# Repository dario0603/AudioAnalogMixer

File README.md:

# Analog Audio Mixer

## Overview

Design and development of a **modular analog audio mixer**, combining circuit simulation and PCB design. The project focuses on audio signal conditioning, equalization, level control, and the integration of multiple input channels into a modular mixer architecture.

The design is divided into two main development areas:

- **LTspice simulations:** individual analog circuit blocks are simulated and evaluated before hardware implementation.
- **KiCad designs:** modular PCB boards are developed to organize the mixer circuitry into functional sections.

The current design includes microphone/line signal conditioning, a three-band equalizer, level and FX-send circuitry, a clipping indicator, and a four-channel mixer board.

The project is still under development. Circuit design, simulation, and PCB integration are ongoing, and the current files should be considered work in progress rather than a finalized hardware design.

## System Architecture

The mixer is organized into modular functional blocks. This approach makes it possible to develop and test each section independently before integrating the complete system.
The input stage provides microphone and line-level signal conditioning. Separate configurations are included for a single microphone/line channel and for two line-level channels, intended for left and right stereo signals.

The signal-conditioning section includes:

- Microphone/line preamplification.
- Three-band tone control.
- Output-level adjustment.
- FX-send circuitry.

### 1. Microphone/Line Preamplifier Circuit

The microphone/line preamplifier circuit provides input signal conditioning and amplification for low-level microphone signals and line-level audio sources. It is designed to adapt different input signal levels to the following stages of the mixer, ensuring proper signal amplification and compatibility with the audio processing circuitry.

### 2. Three-Band Equalizer

The three-band equalizer provides independent control over the low-, mid-, and high-frequency portions of the audio spectrum.

The frequency response is evaluated through LTspice AC analysis. Different equalizer settings are compared to investigate how the circuit affects the audio signal across the frequency range.

### 3. Mixer Unit

This stage combines the signals processed by the input stages (microphone/line preamplifier and three-band equalizer), summing the individual channels to generate the final audio output. The output is provided in differential mode through two dedicated buffer amplifiers, ensuring proper signal driving capability and output impedance.

### 4. Clipping Indicator

A dedicated clipping-indicator circuit is included in the LTspice project.

The circuit uses an LM393 comparator model to detect signal levels approaching the selected clipping threshold. The output can be used to drive an LED, providing a visual indication of excessive signal amplitude.

The comparator circuit is simulated separately to allow its operation and threshold behavior to be evaluated independently of the complete mixer.

## Simulations

### 1. Three-Band Equalizer

**Frequency Response Analysis**

The frequency response of the three-band equalizer is analyzed for different control settings, including low-frequency, mid-frequency, and high-frequency attenuation.

| Low-frequency cut | Mid-frequency cut | High-frequency cut |
|:---:|:---:|:---:|
|  |  |  |

**Flat Frequency Response Analysis**

The overall frequency response is evaluated with all equalizer controls set to their neutral positions.

**Monte Carlo Frequency Response Analysis**

A Monte Carlo analysis is performed to evaluate the effect of component tolerances on the equalizer response, considering 1% resistor tolerances (0603 package) and 10% ceramic X7R capacitor tolerances.

### 2. Microphone/Line Preamplifier

**AC Frequency Response Analysis**

The frequency response of the line and XLR preamplifier configurations is evaluated through LTspice AC analysis to characterize their behavior across the audio frequency range.

**Line Preamplifier:**

**XLR Preamplifier:**

**Transient Response Analysis – 5 kHz Differential Input**

A 5 kHz differential sinusoidal signal is applied to the XLR preamplifier to evaluate its transient response under maximum and minimum gain configurations.

**Input Signal:**

**Maximum Gain Configuration:**

**Minimum Gain Configuration:**

**Monte Carlo Transient Analysis**

A Monte Carlo simulation consisting of 300 runs is performed to evaluate the variability of the XLR preamplifier transient response due to component tolerances, considering both maximum and minimum gain configurations.

**Maximum Gain Configuration:**

**Minimum Gain Configuration:**

**Noise Analysis**

LTspice noise analysis is performed to evaluate the output noise spectral density of the preamplifier stages. Different operational-amplifier configurations are compared to investigate their noise contributions.

The noise simulations are still being refined, particularly regarding the accuracy of the operational-amplifier noise models and their consistency with datasheet specifications.

### 3. Mixer

**Transient Response Analysis**

Transient simulations are performed to evaluate the time-domain behavior of the mixer circuit.

**Monte Carlo Transient Analysis**

A Monte Carlo simulation consisting of 300 runs is performed to investigate output voltage variations caused by component tolerances.

.png)

## PCB Design

The PCB development is carried out in KiCad. The modular approach separates the main mixer board from the input signal-conditioning circuitry.

### 1. Four-Channel Mixer Board

The `4ChannelMixerBoard` project contains the PCB design and schematic for the four-channel mixer board.

The board is intended to provide the central platform for combining the individual audio channels.

### 2. Single-Channel Microphone/Line Board

The `SignalConditioning - OneChannel - Mic-Line` project contains the signal-conditioning design for a single microphone/line input channel.
The PCB layout brings the microphone/line preamplifier, three-band equalizer, level and FX-send circuitry, and power supply together on a single board.

The project includes the following schematic sections:

- Microphone/line preamplifier.
- Three-band equalizer.
- Level control and FX-send circuitry.
- Power supply.

### 3. Two-Channel Line Board

The `SignalConditioning - TwoChannels - R-L-Line` project contains a two-channel signal-conditioning configuration intended for right and left line-level signals.

Its schematic is organized around the same functional blocks as the single-channel version, adapted for a stereo input configuration.

## Repository Structure

```text
.
├── README.md
│
├── AudioMixer - LTSpice/
│   ├── 3bEq/
│   │   ├── AudioMixer - 3bEq.asc
│   │   ├── NE5532.sub
│   │   └── Montecarlo/
│   │
│   ├── ClippingLed/
│   │   ├── ClippingLed.asc
│   │   └── lm393.lib
│   │
│   └── Mic-Line amplifier/
│       ├── AudioMixer - Mic-Line-amp.asc
│       └── NE5532.sub
│
├── AudioMixer - ModularBoards/
│   ├── spec.txt
│   │
│   ├── 4ChannelMixerBoard/
│   │   ├── Mixer_circuit.kicad_pro
│   │   ├── Mixer_circuit.kicad_sch
│   │   └── Mixer_circuit.kicad_pcb
│   │
│   ├── SignalConditioning - OneChannel - Mic-Line/
│   │   ├── AudioMixer.kicad_pro
│   │   ├── AudioMixer.kicad_sch
│   │   ├── AudioMixer.kicad_pcb
│   │   ├── Mic-Line_preamp.kicad_sch
│   │   ├── 3_band_equalizer.kicad_sch
│   │   ├── Level_and_FXSend.kicad_sch
│   │   └── Power_supply.kicad_sch
│   │
│   └── SignalConditioning - TwoChannels - R-L-Line/
│       ├── AudioMixer.kicad_pro
│       ├── AudioMixer.kicad_sch
│       ├── AudioMixer.kicad_pcb
│       ├── Mic-Line_preamp.kicad_sch
│       ├── 3_band_equalizer.kicad_sch
│       ├── Level_and_FXSend.kicad_sch
│       └── Power_supply.kicad_sch
│
└── img/
```

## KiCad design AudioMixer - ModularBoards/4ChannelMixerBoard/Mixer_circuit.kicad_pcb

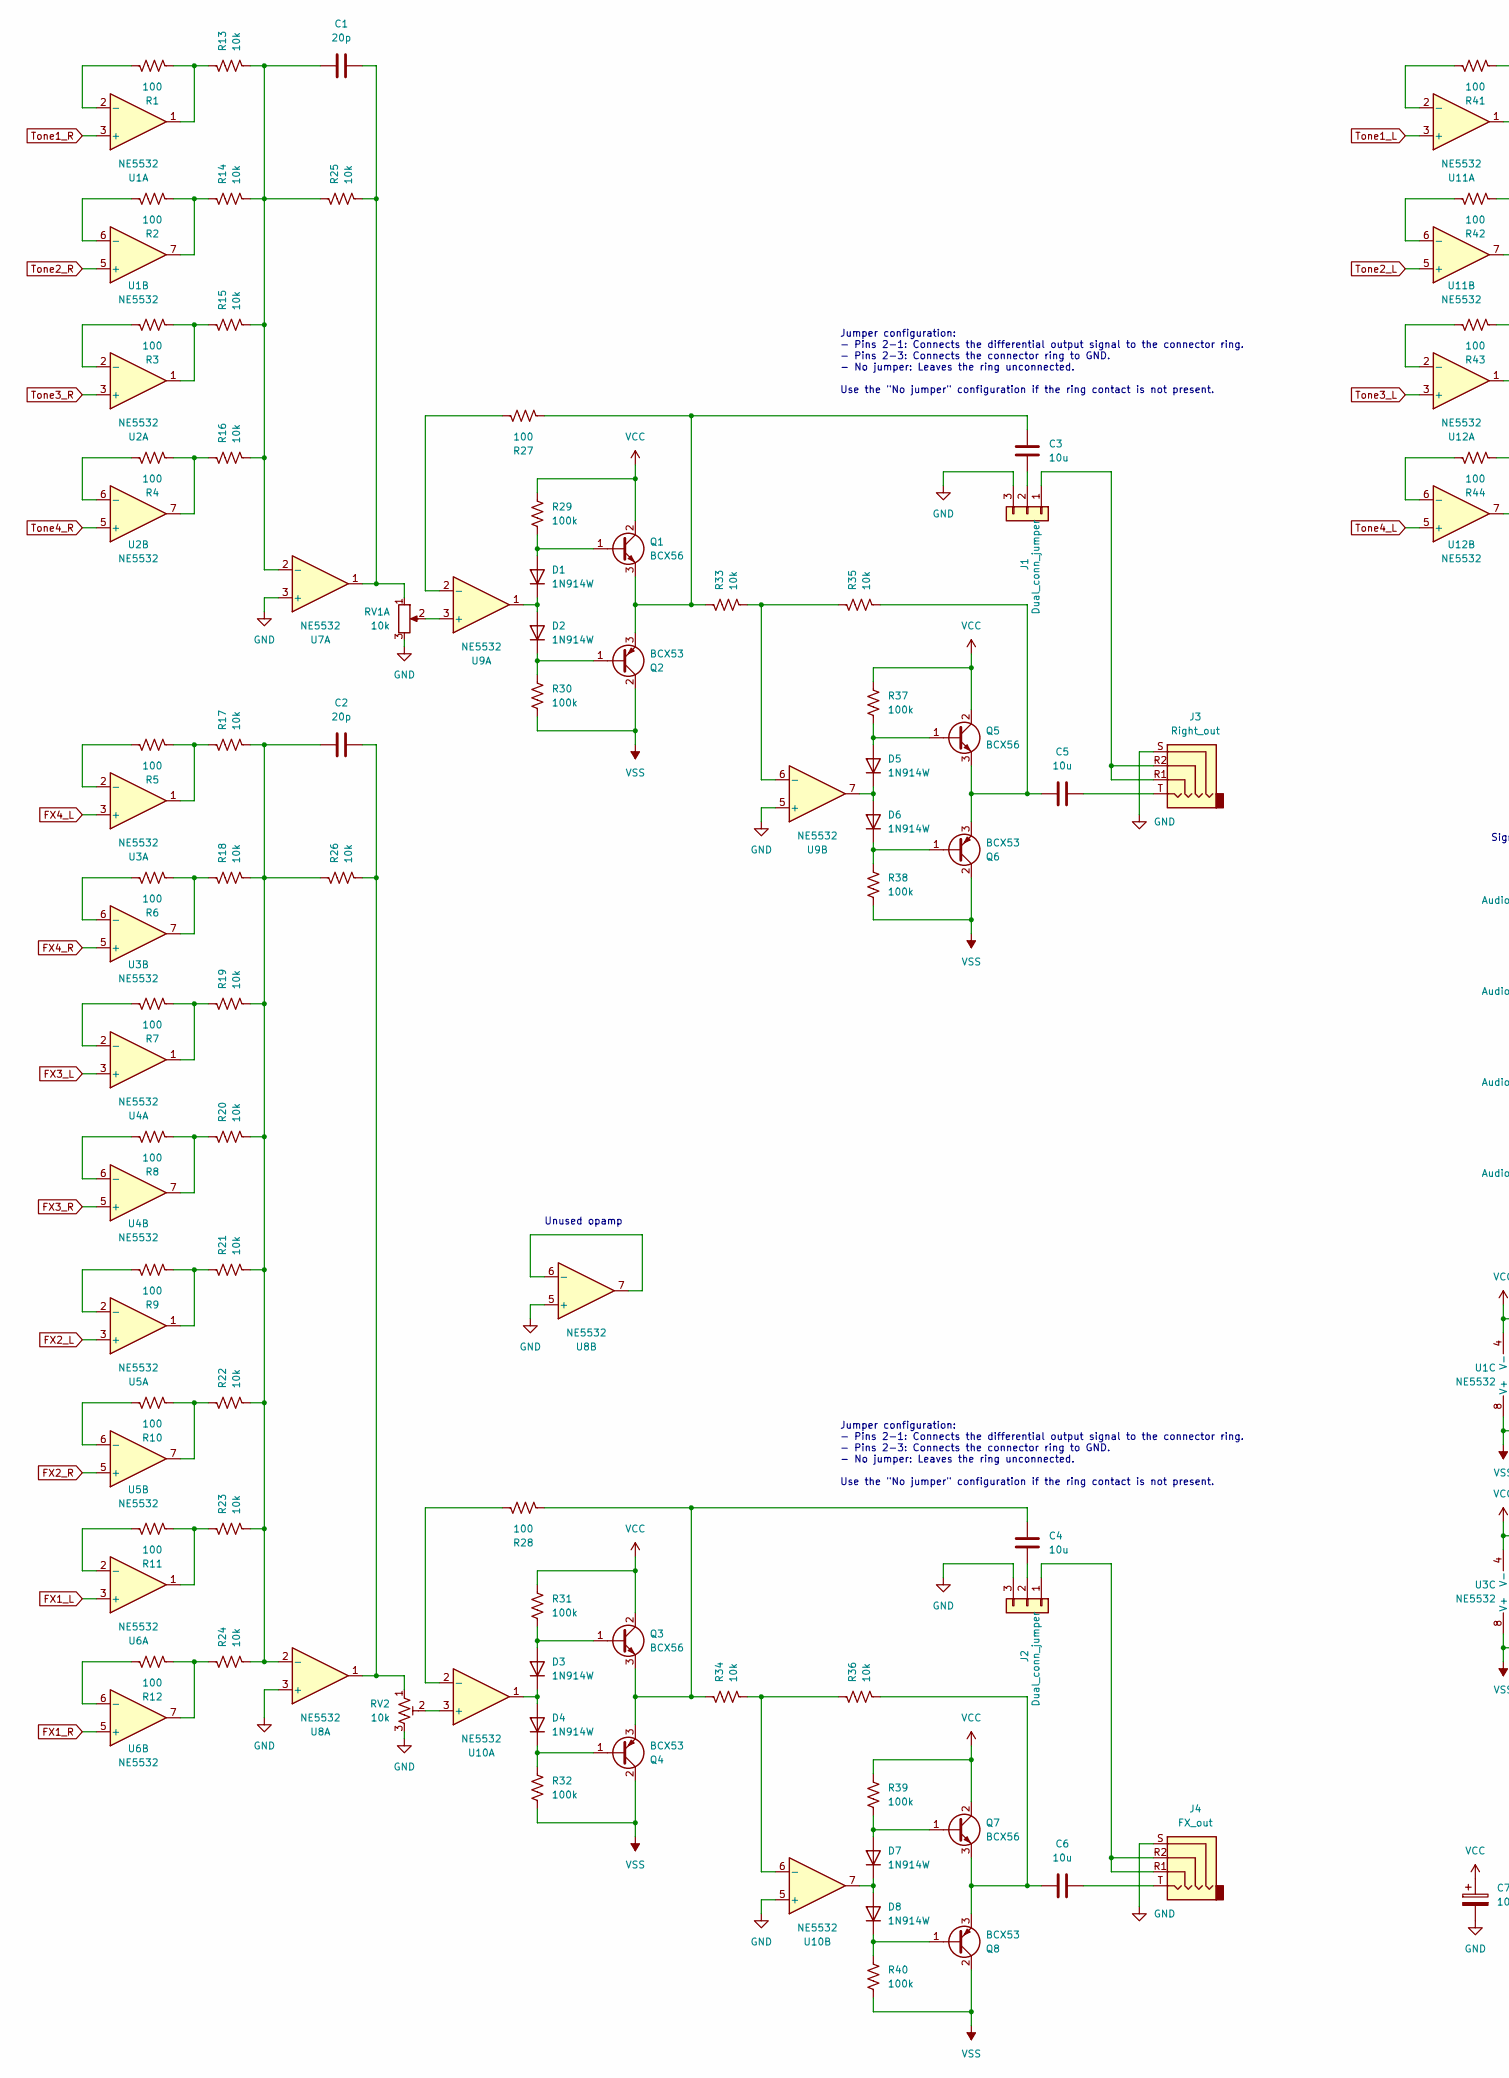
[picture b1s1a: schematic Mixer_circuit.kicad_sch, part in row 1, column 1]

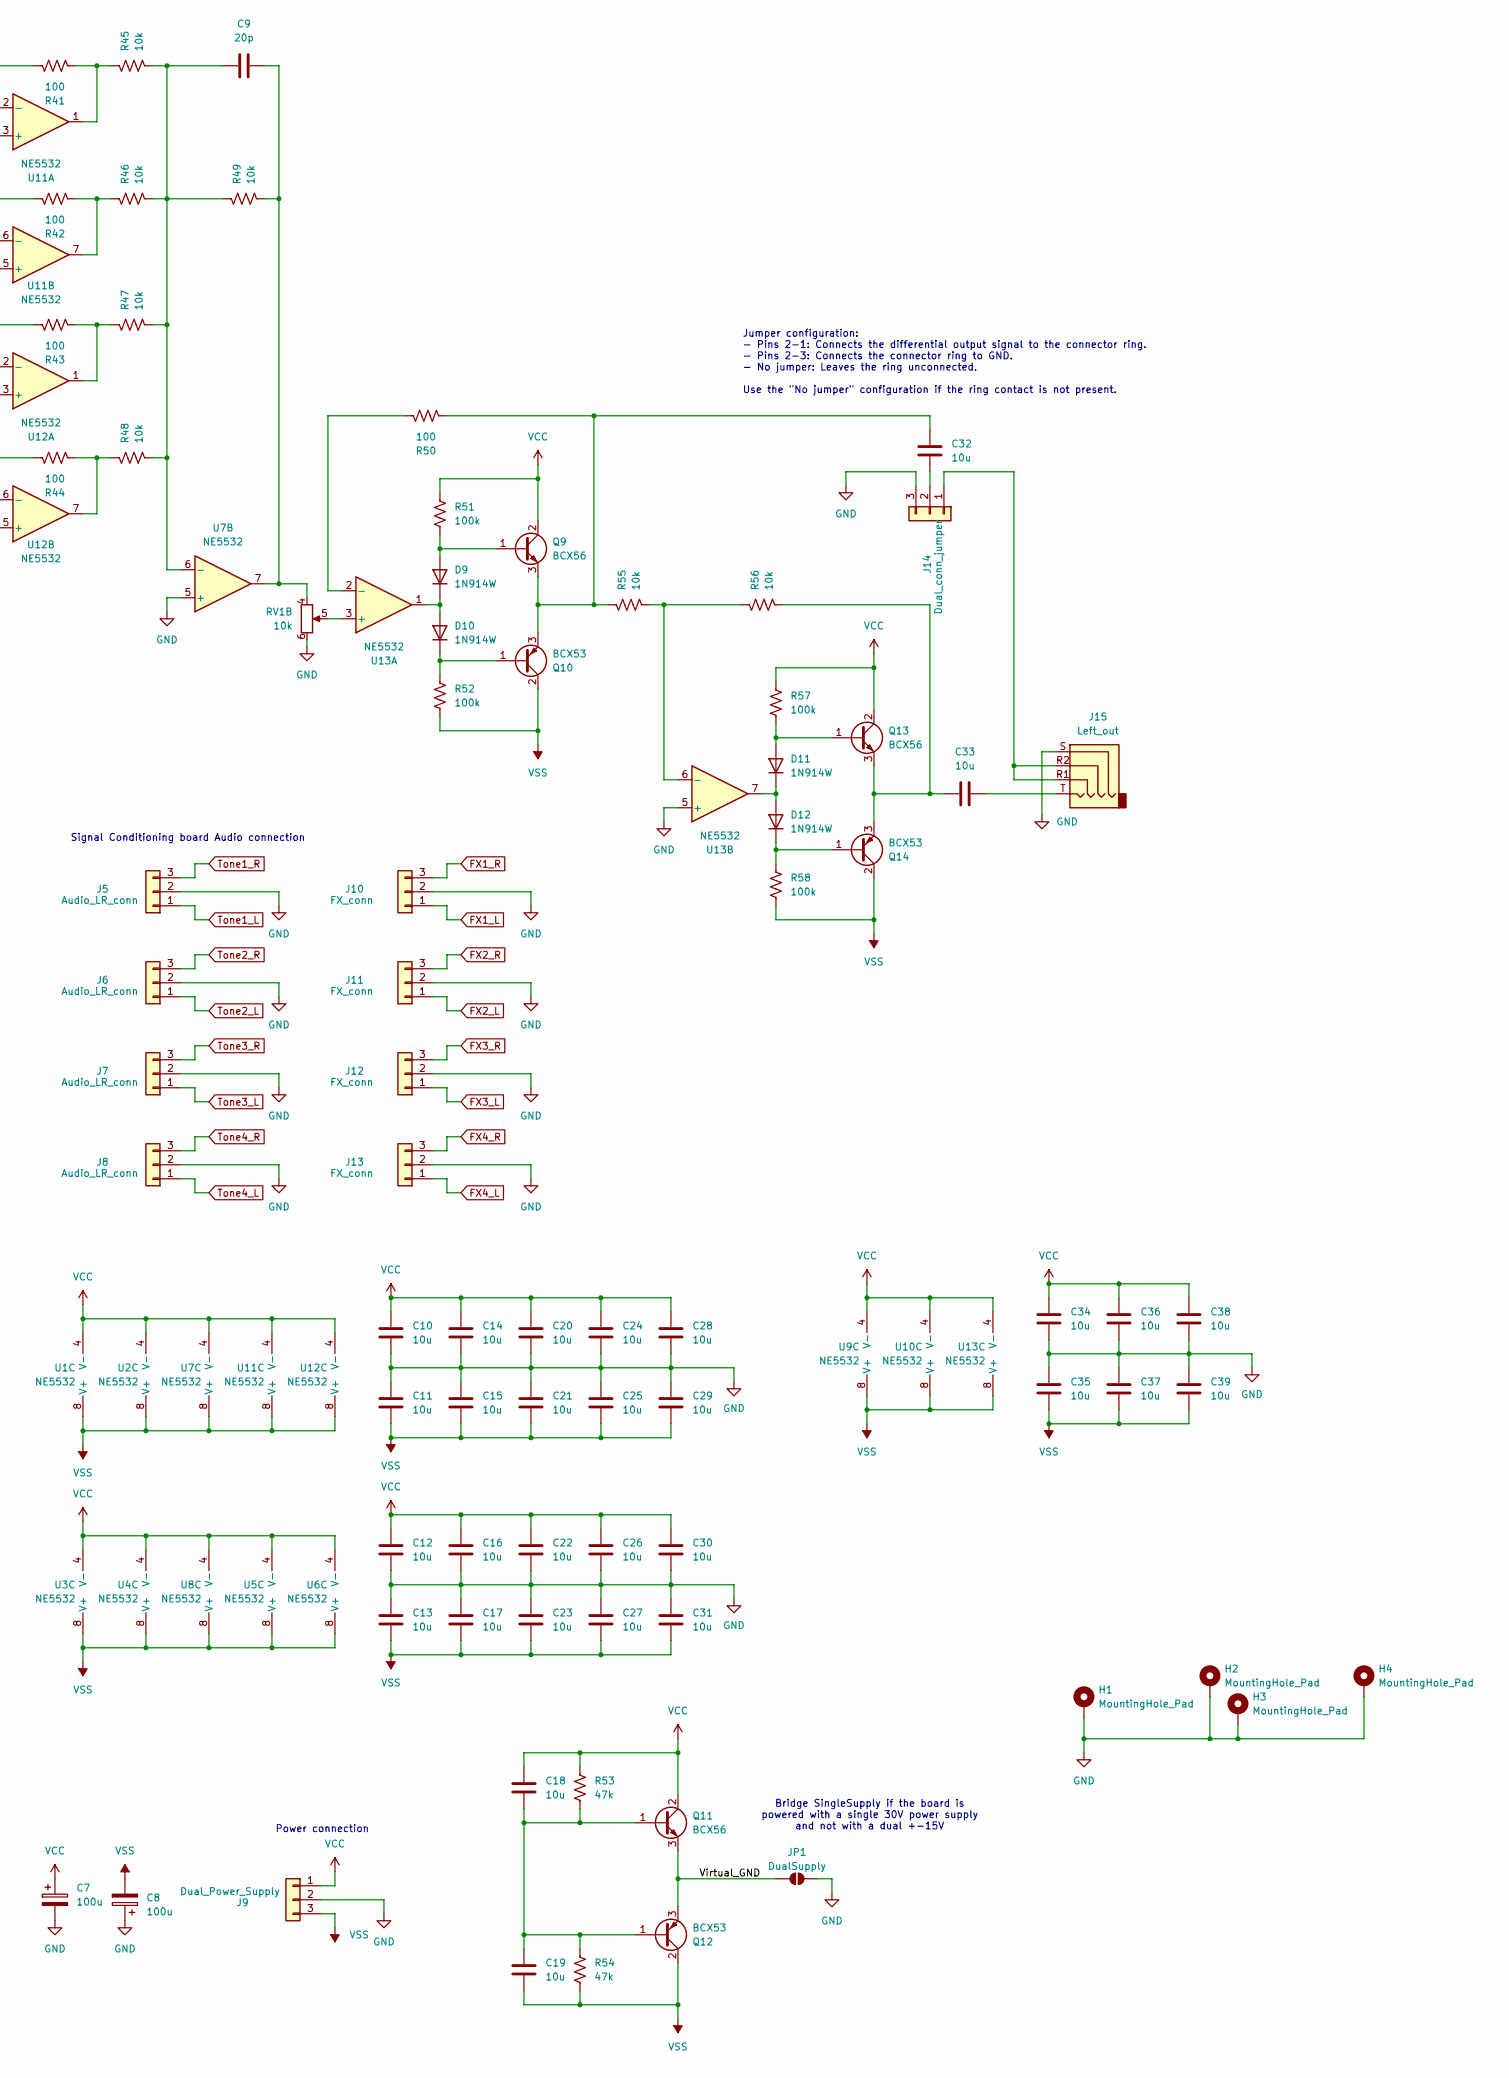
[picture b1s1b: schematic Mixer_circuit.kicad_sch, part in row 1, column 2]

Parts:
C1, C2, C9: 20p; C_0603_1608Metric_Pad1.08x0.95mm_HandSolder
C3, C4, C5, C6, C10, C11, C12, C13, C14, C15, C16, C17, C18, C19, C20, C21, C22, C23, C24, C25, C26, C27, C28, C29, C30, C31, C32, C33, C34, C35, C36, C37, C38, C39: 10u; C_0805_2012Metric_Pad1.18x1.45mm_HandSolder
C7, C8: 100u; CP_Radial_D8.0mm_P3.50mm
D1, D2, D3, D4, D5, D6, D7, D8, D9, D10, D11, D12: 1N914W; D_SOD-123
H1, H2, H3, H4: MountingHole_Pad; MountingHole_3.2mm_M3_DIN965_Pad_TopBottom
J1, J2, J14: Dual_conn_jumper; PinHeader_1x03_P2.54mm_Vertical
J3: Right_out; Jack_3.5mm_PJ320E_Horizontal
J4: FX_out; Jack_3.5mm_PJ320E_Horizontal
J5, J6, J7, J8: Audio_LR_conn; PinHeader_1x03_P2.54mm_Vertical
J9: Dual_Power_Supply; PinHeader_1x03_P2.54mm_Vertical
J10, J11, J12, J13: FX_conn; PinHeader_1x03_P2.54mm_Vertical
J15: Left_out; Jack_3.5mm_PJ320E_Horizontal
JP1: DualSupply; SolderJumper-2_P1.3mm_Open_RoundedPad1.0x1.5mm
Q1, Q3, Q5, Q7, Q9, Q11, Q13: BCX56; SOT-89-3
Q2, Q4, Q6, Q8, Q10, Q12, Q14: BCX53; SOT-89-3
R1, R2, R3, R4, R5, R6, R7, R8, R9, R10, R11, R12, R27, R28, R41, R42, R43, R44, R50: 100; R_0603_1608Metric_Pad0.98x0.95mm_HandSolder
R13, R14, R15, R16, R17, R18, R19, R20, R21, R22, R23, R24, R25, R26, R33, R34, R35, R36, R45, R46, R47, R48, R49, R55, R56: 10k; R_0603_1608Metric_Pad0.98x0.95mm_HandSolder
R29, R30, R31, R32, R37, R38, R39, R40, R51, R52, R57, R58: 100k; R_0603_1608Metric_Pad0.98x0.95mm_HandSolder
R53, R54: 47k; R_0603_1608Metric_Pad0.98x0.95mm_HandSolder
RV1: 10k; Potentiometer_Alps_RK097_Dual_Horizontal
RV2: 10k; Potentiometer_Alps_RK097_Single_Horizontal
U1, U2, U3, U4, U5, U6, U7, U8, U9, U10, U11, U12, U13: NE5532; SOIC-8_3.9x4.9mm_P1.27mm

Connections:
/Virtual_GND: JP1.1 (A), Q11.3 (E), Q12.3 (E)
FX1_L: J10.1, U6.3 (+)
FX1_R: J10.3, U6.5 (+)
FX2_L: J11.1, U5.3 (+)
FX2_R: J11.3, U5.5 (+)
FX3_L: J12.1, U4.3 (+)
FX3_R: J12.3, U4.5 (+)
FX4_L: J13.1, U3.3 (+)
FX4_R: J13.3, U3.5 (+)
GND: C7.2, C8.1, C10.2, C11.1, C12.2, C13.1, C14.2, C15.1, C16.2, C17.1, C20.2, C21.1, C22.2, C23.1, C24.2, C25.1, C26.2, C27.1, C28.2, C29.1, C30.2, C31.1, C34.2, C35.1, C36.2, C37.1, C38.2, C39.1, H1.1, H2.1, H3.1, H4.1, J1.3, J2.3, J3.S, J4.S, J5.2, J6.2, J7.2, J8.2, J9.2, J10.2, J11.2, J12.2, J13.2, J14.3, J15.S, JP1.2 (B), RV1.3, RV1.6, RV2.3, U7.3 (+), U7.5 (+), U8.3 (+), U8.5 (+), U9.5 (+), U10.5 (+), U13.5 (+)
unnamed: C1.2, R25.2, RV1.1, U7.1
unnamed: C2.2, R26.2, RV2.1, U8.1
unnamed: C5.2, J3.T
unnamed: C6.2, J4.T
unnamed: C9.2, R49.2, RV1.4, U7.7
unnamed: C33.2, J15.T
unnamed: D1.2 (A), Q1.1 (B), R29.2
unnamed: D1.1 (K), D2.2 (A), U9.1
unnamed: D2.1 (K), Q2.1 (B), R30.1
unnamed: D3.2 (A), Q3.1 (B), R31.2
unnamed: D3.1 (K), D4.2 (A), U10.1
unnamed: D4.1 (K), Q4.1 (B), R32.1
unnamed: D5.2 (A), Q5.1 (B), R37.2
unnamed: D5.1 (K), D6.2 (A), U9.7
unnamed: D6.1 (K), Q6.1 (B), R38.1
unnamed: D7.2 (A), Q7.1 (B), R39.2
unnamed: D7.1 (K), D8.2 (A), U10.7
unnamed: D8.1 (K), Q8.1 (B), R40.1
unnamed: D9.2 (A), Q9.1 (B), R51.2
unnamed: D9.1 (K), D10.2 (A), U13.1
unnamed: D10.1 (K), Q10.1 (B), R52.1
unnamed: D11.2 (A), Q13.1 (B), R57.2
unnamed: D11.1 (K), D12.2 (A), U13.7
unnamed: D12.1 (K), Q14.1 (B), R58.1
unnamed: J1.1, J3.R1, J3.R2
unnamed: C3.2, J1.2
unnamed: J2.1, J4.R1, J4.R2
unnamed: C4.2, J2.2
unnamed: J14.1, J15.R1, J15.R2
unnamed: C32.2, J14.2
unnamed: C3.1, Q1.3 (E), Q2.3 (E), R27.2, R33.1
unnamed: C4.1, Q3.3 (E), Q4.3 (E), R28.2, R34.1
unnamed: C5.1, Q5.3 (E), Q6.3 (E), R35.2
unnamed: C6.1, Q7.3 (E), Q8.3 (E), R36.2
unnamed: C32.1, Q9.3 (E), Q10.3 (E), R50.2, R55.1
unnamed: C18.2, C19.1, Q11.1 (B), Q12.1 (B), R53.2, R54.1
unnamed: C33.1, Q13.3 (E), Q14.3 (E), R56.2
unnamed: R1.2, R13.1, U1.1
unnamed: R10.2, R22.1, U5.7
unnamed: R11.2, R23.1, U6.1
unnamed: R12.2, R24.1, U6.7
unnamed: R2.2, R14.1, U1.7
unnamed: R3.2, R15.1, U2.1
unnamed: R4.2, R16.1, U2.7
unnamed: R5.2, R17.1, U3.1
unnamed: R6.2, R18.1, U3.7
unnamed: R7.2, R19.1, U4.1
unnamed: R8.2, R20.1, U4.7
unnamed: R9.2, R21.1, U5.1
unnamed: R41.2, R45.1, U11.1
unnamed: R42.2, R46.1, U11.7
unnamed: R43.2, R47.1, U12.1
unnamed: R44.2, R48.1, U12.7
unnamed: R1.1, U1.2 (-)
unnamed: R2.1, U1.6 (-)
unnamed: R3.1, U2.2 (-)
unnamed: R4.1, U2.6 (-)
unnamed: R5.1, U3.2 (-)
unnamed: R6.1, U3.6 (-)
unnamed: R7.1, U4.2 (-)
unnamed: R8.1, U4.6 (-)
unnamed: R9.1, U5.2 (-)
unnamed: R10.1, U5.6 (-)
unnamed: R11.1, U6.2 (-)
unnamed: R12.1, U6.6 (-)
unnamed: C1.1, R13.2, R14.2, R15.2, R16.2, R25.1, U7.2 (-)
unnamed: C9.1, R45.2, R46.2, R47.2, R48.2, R49.1, U7.6 (-)
unnamed: C2.1, R17.2, R18.2, R19.2, R20.2, R21.2, R22.2, R23.2, R24.2, R26.1, U8.2 (-)
unnamed: U8.6 (-), U8.7
unnamed: RV1.2, U9.3 (+)
unnamed: R27.1, U9.2 (-)
unnamed: R33.2, R35.1, U9.6 (-)
unnamed: RV2.2, U10.3 (+)
unnamed: R28.1, U10.2 (-)
unnamed: R34.2, R36.1, U10.6 (-)
unnamed: R41.1, U11.2 (-)
unnamed: R42.1, U11.6 (-)
unnamed: R43.1, U12.2 (-)
unnamed: R44.1, U12.6 (-)
unnamed: RV1.5, U13.3 (+)
unnamed: R50.1, U13.2 (-)
unnamed: R55.2, R56.1, U13.6 (-)
Tone1_L: J5.1, U11.3 (+)
Tone1_R: J5.3, U1.3 (+)
Tone2_L: J6.1, U11.5 (+)
Tone2_R: J6.3, U1.5 (+)
Tone3_L: J7.1, U12.3 (+)
Tone3_R: J7.3, U2.3 (+)
Tone4_L: J8.1, U12.5 (+)
Tone4_R: J8.3, U2.5 (+)
VCC: C7.1, C10.1, C12.1, C14.1, C16.1, C18.1, C20.1, C22.1, C24.1, C26.1, C28.1, C30.1, C34.1, C36.1, C38.1, J9.1, Q1.2 (C), Q3.2 (C), Q5.2 (C), Q7.2 (C), Q9.2 (C), Q11.2 (C), Q13.2 (C), R29.1, R31.1, R37.1, R39.1, R51.1, R53.1, R57.1, U1.4 (V-), U2.4 (V-), U3.4 (V-), U4.4 (V-), U5.4 (V-), U6.4 (V-), U7.4 (V-), U8.4 (V-), U9.4 (V-), U10.4 (V-), U11.4 (V-), U12.4 (V-), U13.4 (V-)
VSS: C8.2, C11.2, C13.2, C15.2, C17.2, C19.2, C21.2, C23.2, C25.2, C27.2, C29.2, C31.2, C35.2, C37.2, C39.2, J9.3, Q2.2 (C), Q4.2 (C), Q6.2 (C), Q8.2 (C), Q10.2 (C), Q12.2 (C), Q14.2 (C), R30.2, R32.2, R38.2, R40.2, R52.2, R54.2, R58.2, U1.8 (V+), U2.8 (V+), U3.8 (V+), U4.8 (V+), U5.8 (V+), U6.8 (V+), U7.8 (V+), U8.8 (V+), U9.8 (V+), U10.8 (V+), U11.8 (V+), U12.8 (V+), U13.8 (V+)

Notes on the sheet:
Power connection
Signal Conditioning board Audio connection
Jumper configuration: - Pins 2-1: Connects the differential output signal to the connector ring. - Pins 2-3: Connects the connector ring to GND. - No jumper: Leaves the ring unconnected. Use the "No jumper" configuration if the ring contact is not present.
Bridge SingleSupply if the board is powered with a single 30V power supply and not with a dual +-15V
Unused opamp

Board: 2 copper layers, 158 parts (0 on the bottom side), 102 nets, no tracks yet.

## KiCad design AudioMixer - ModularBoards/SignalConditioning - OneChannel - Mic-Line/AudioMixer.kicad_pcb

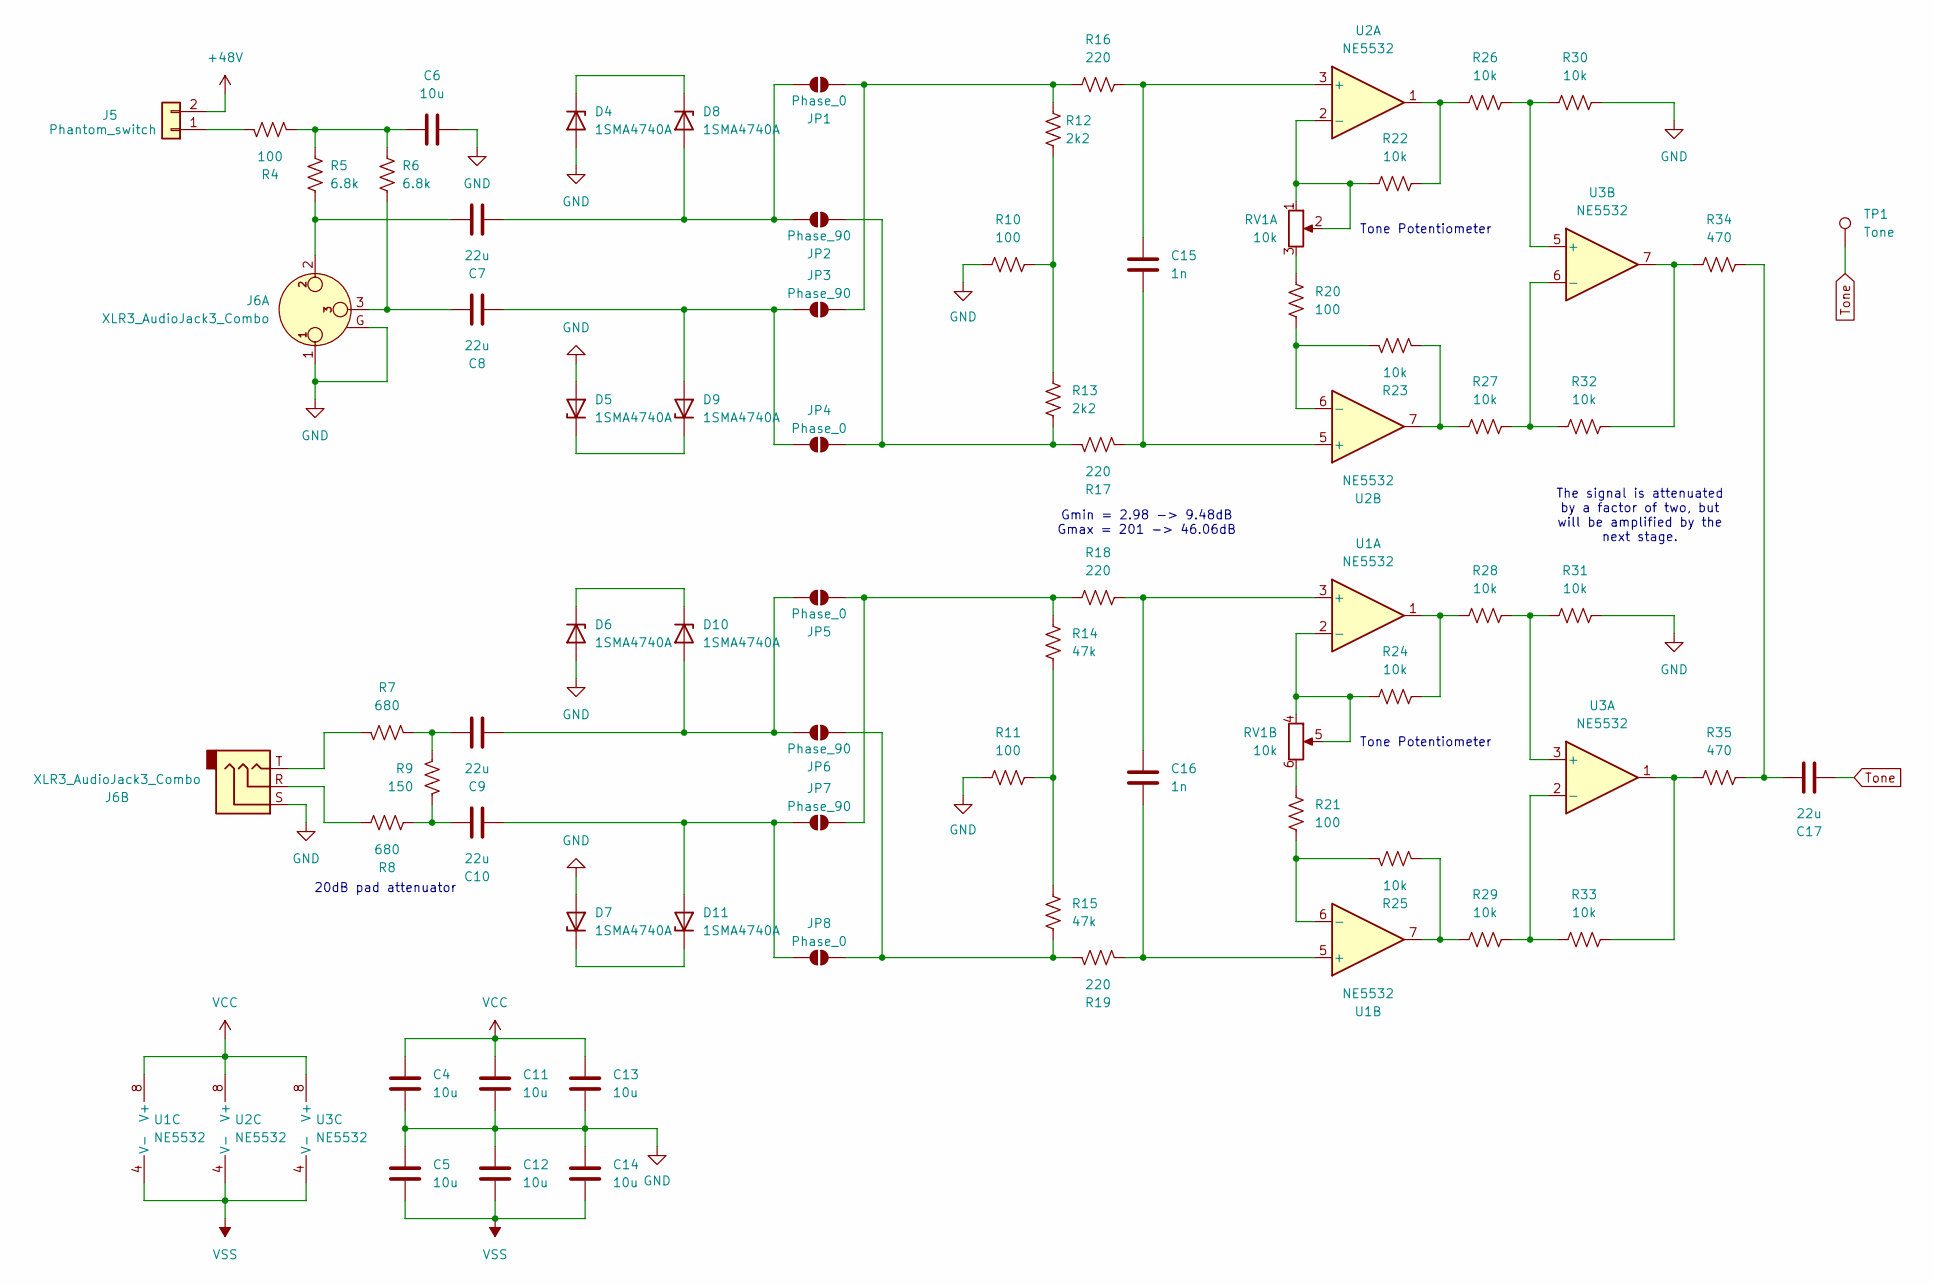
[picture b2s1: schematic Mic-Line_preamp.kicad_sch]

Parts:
C4, C5, C6, C11, C12, C13, C14: 10u; C_0805_2012Metric_Pad1.18x1.45mm_HandSolder
C7, C8, C9, C10, C17: 22u; C_0805_2012Metric_Pad1.18x1.45mm_HandSolder
C15, C16: 1n; C_0603_1608Metric_Pad1.08x0.95mm_HandSolder
D4, D5, D6, D7, D8, D9, D10, D11: 1SMA4740A; D_SMA
J5: Phantom_switch; PinHeader_1x02_P2.54mm_Vertical
J6: XLR3_AudioJack3_Combo; Jack_XLR-6.35mm_Neutrik_NCJ6FI-H_Horizontal
JP1, JP4, JP5, JP8: Phase_0; SolderJumper-2_P1.3mm_Open_RoundedPad1.0x1.5mm
JP2, JP3, JP6, JP7: Phase_90; SolderJumper-2_P1.3mm_Open_RoundedPad1.0x1.5mm
R4: 100; R_1206_3216Metric_Pad1.30x1.75mm_HandSolder
R5, R6: 6.8k; R_1206_3216Metric_Pad1.30x1.75mm_HandSolder
R7, R8: 680; R_0603_1608Metric_Pad0.98x0.95mm_HandSolder
R9: 150; R_0603_1608Metric_Pad0.98x0.95mm_HandSolder
R10, R11, R20, R21: 100; R_0603_1608Metric_Pad0.98x0.95mm_HandSolder
R12, R13: 2k2; R_0603_1608Metric_Pad0.98x0.95mm_HandSolder
R14, R15: 47k; R_0603_1608Metric_Pad0.98x0.95mm_HandSolder
R16, R17, R18, R19: 220; R_0603_1608Metric_Pad0.98x0.95mm_HandSolder
R22, R23, R24, R25, R26, R27, R28, R29, R30, R31, R32, R33: 10k; R_0603_1608Metric_Pad0.98x0.95mm_HandSolder
R34, R35: 470; R_0603_1608Metric_Pad0.98x0.95mm_HandSolder
RV1: 10k; Potentiometer_Alps_RK097_Dual_Horizontal
TP1: Tone; TestPoint_Pad_D1.0mm
U1, U2, U3: NE5532; SOIC-8_3.9x4.9mm_P1.27mm

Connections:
+48V: J5.2; also elsewhere on the board
GND: C4.2, C5.1, C6.1, C11.2, C12.1, C13.2, C14.1, D4.2 (A), D5.2 (A), D6.2 (A), D7.2 (A), J6.1, J6.G, J6.S, R10.1, R11.2, R30.1, R31.1; also elsewhere on the board
unnamed: C6.2, R4.1, R5.2, R6.2
unnamed: C7.1, J6.2, R5.1
unnamed: C8.1, J6.3, R6.1
unnamed: C9.1, R7.2, R9.2
unnamed: C10.1, R8.2, R9.1
unnamed: C17.1, R34.2, R35.2
unnamed: D4.1 (K), D8.1 (K)
unnamed: D5.1 (K), D9.1 (K)
unnamed: C7.2, D8.2 (A), JP1.1 (A), JP2.1 (A)
unnamed: C8.2, D9.2 (A), JP3.1 (A), JP4.1 (A)
unnamed: C9.2, D10.2 (A), JP5.1 (A), JP6.1 (A)
unnamed: D6.1 (K), D10.1 (K)
unnamed: C10.2, D11.2 (A), JP7.1 (A), JP8.1 (A)
unnamed: D7.1 (K), D11.1 (K)
unnamed: J5.1, R4.2
unnamed: J6.R, R8.1
unnamed: J6.T, R7.1
unnamed: JP1.2 (B), JP3.2 (B), R12.1, R16.2
unnamed: JP2.2 (B), JP4.2 (B), R13.2, R17.2
unnamed: JP5.2 (B), JP7.2 (B), R14.1, R18.2
unnamed: JP6.2 (B), JP8.2 (B), R15.2, R19.2
unnamed: R10.2, R12.2, R13.1
unnamed: R11.1, R14.2, R15.1
unnamed: R20.1, RV1.3
unnamed: R21.1, RV1.6
unnamed: R22.1, R26.2, U2.1
unnamed: R23.1, R27.2, U2.7
unnamed: R24.1, R28.2, U1.1
unnamed: R25.1, R29.2, U1.7
unnamed: R32.1, R34.1, U3.7
unnamed: R33.1, R35.1, U3.1
unnamed: C16.1, R18.1, U1.3 (+)
unnamed: R24.2, RV1.4, RV1.5, U1.2 (-)
unnamed: C16.2, R19.1, U1.5 (+)
unnamed: R21.2, R25.2, U1.6 (-)
unnamed: C15.1, R16.1, U2.3 (+)
unnamed: R22.2, RV1.1, RV1.2, U2.2 (-)
unnamed: C15.2, R17.1, U2.5 (+)
unnamed: R20.2, R23.2, U2.6 (-)
unnamed: R28.1, R31.2, U3.3 (+)
unnamed: R29.1, R33.2, U3.2 (-)
unnamed: R26.1, R30.2, U3.5 (+)
unnamed: R27.1, R32.2, U3.6 (-)
Tone: C17.2, TP1.1; also elsewhere on the board
VCC: C4.1, C11.1, C13.1, U1.8 (V+), U2.8 (V+), U3.8 (V+); also elsewhere on the board
VSS: C5.2, C12.2, C14.2, U1.4 (V-), U2.4 (V-), U3.4 (V-); also elsewhere on the board

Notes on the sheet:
Gmin = 2.98 -> 9.48dB Gmax = 201 -> 46.06dB
Tone Potentiometer
20dB pad attenuator
The signal is attenuated by a factor of two, but will be amplified by the next stage.

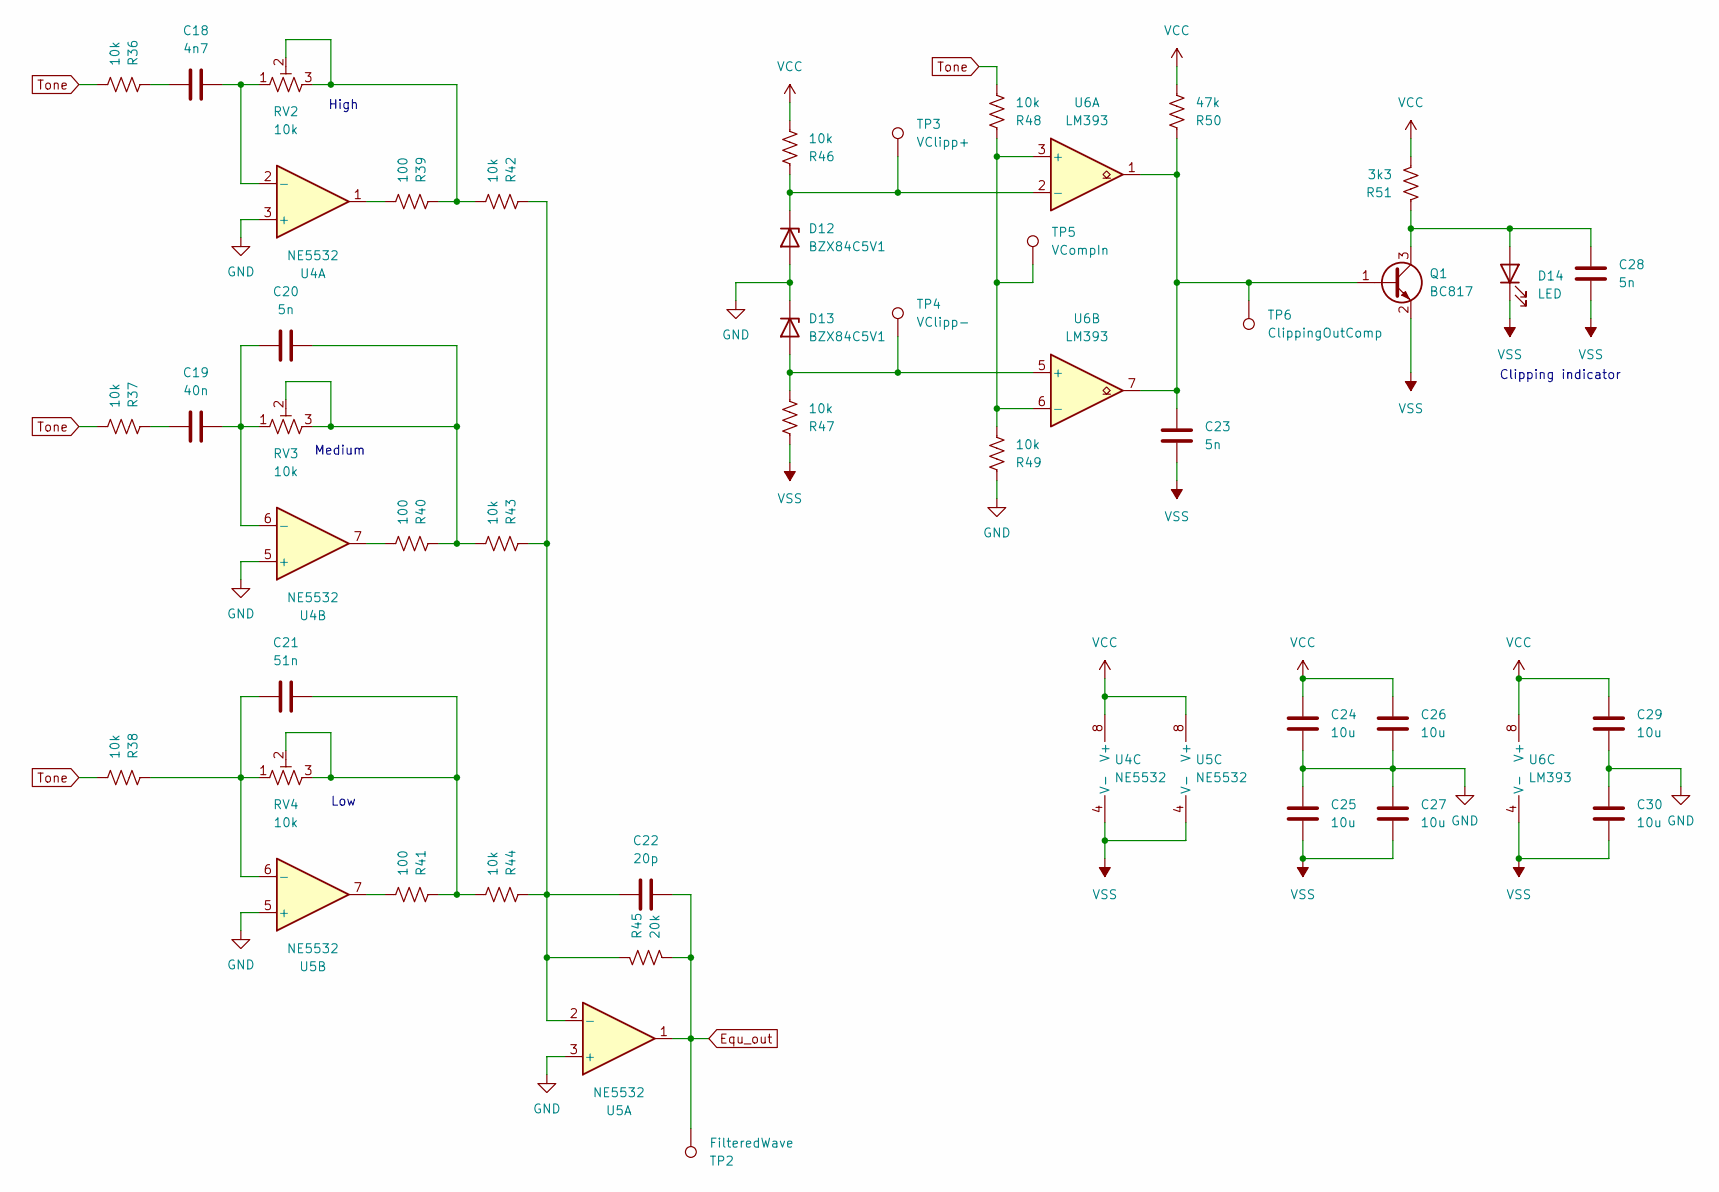
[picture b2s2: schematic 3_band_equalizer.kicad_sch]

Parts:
C18: 4n7; C_0603_1608Metric_Pad1.08x0.95mm_HandSolder
C19: 40n; C_0603_1608Metric_Pad1.08x0.95mm_HandSolder
C20, C23, C28: 5n; C_0603_1608Metric_Pad1.08x0.95mm_HandSolder
C21: 51n; C_0603_1608Metric_Pad1.08x0.95mm_HandSolder
C22: 20p; C_0603_1608Metric_Pad1.08x0.95mm_HandSolder
C24, C25, C26, C27, C29, C30: 10u; C_0805_2012Metric_Pad1.18x1.45mm_HandSolder
D12, D13: BZX84C5V1; SOT-23
D14: LED; LED_D3.0mm
Q1: BC817; SOT-23
R36, R37, R38, R42, R43, R44, R46, R47, R48, R49: 10k; R_0603_1608Metric_Pad0.98x0.95mm_HandSolder
R39, R40, R41: 100; R_0603_1608Metric_Pad0.98x0.95mm_HandSolder
R45: 20k; R_0603_1608Metric_Pad0.98x0.95mm_HandSolder
R50: 47k; R_0603_1608Metric_Pad0.98x0.95mm_HandSolder
R51: 3k3; R_0603_1608Metric_Pad0.98x0.95mm_HandSolder
RV2, RV3, RV4: 10k; Potentiometer_Alps_RK097_Single_Horizontal
TP2: FilteredWave; TestPoint_Pad_D1.0mm
TP3: VClipp+; TestPoint_Pad_D1.0mm
TP4: VClipp-; TestPoint_Pad_D1.0mm
TP5: VCompIn; TestPoint_Pad_D1.0mm
TP6: ClippingOutComp; TestPoint_Pad_D1.0mm
U4, U5: NE5532; SOIC-8_3.9x4.9mm_P1.27mm
U6: LM393; SOIC-8_3.9x4.9mm_P1.27mm

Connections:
Equ_out: C22.2, R45.2, TP2.1, U5.1; also elsewhere on the board
GND: C24.2, C25.1, C26.2, C27.1, C29.2, C30.1, D12.1 (A), D13.3 (K), R49.1, U4.3 (+), U4.5 (+), U5.3 (+), U5.5 (+); also elsewhere on the board
unnamed: C18.2, R36.1
unnamed: C19.2, R37.1
unnamed: C20.1, R40.1, R43.2, RV3.2, RV3.3
unnamed: C21.1, R41.1, R44.2, RV4.2, RV4.3
unnamed: D12.3 (K), R46.1, TP3.1, U6.2 (-)
unnamed: D13.1 (A), R47.2, TP4.1, U6.5 (+)
unnamed: C28.1, D14.2 (A), Q1.3 (C), R51.1
unnamed: C23.1, Q1.1 (B), R50.1, TP6.1, U6.1, U6.7
unnamed: R39.1, R42.2, RV2.2, RV2.3
unnamed: R39.2, U4.1
unnamed: R40.2, U4.7
unnamed: R41.2, U5.7
unnamed: C18.1, RV2.1, U4.2 (-)
unnamed: C19.1, C20.2, RV3.1, U4.6 (-)
unnamed: C22.1, R42.1, R43.1, R44.1, R45.1, U5.2 (-)
unnamed: C21.2, R38.1, RV4.1, U5.6 (-)
unnamed: R48.1, R49.2, TP5.1, U6.3 (+), U6.6 (-)
Tone: R36.2, R37.2, R38.2, R48.2; also elsewhere on the board
VCC: C24.1, C26.1, C29.1, R46.2, R50.2, R51.2, U4.8 (V+), U5.8 (V+), U6.8 (V+); also elsewhere on the board
VSS: C23.2, C25.2, C27.2, C28.2, C30.2, D14.1 (K), Q1.2 (E), R47.1, U4.4 (V-), U5.4 (V-), U6.4 (V-); also elsewhere on the board

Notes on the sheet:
High
Medium
Clipping indicator
Low

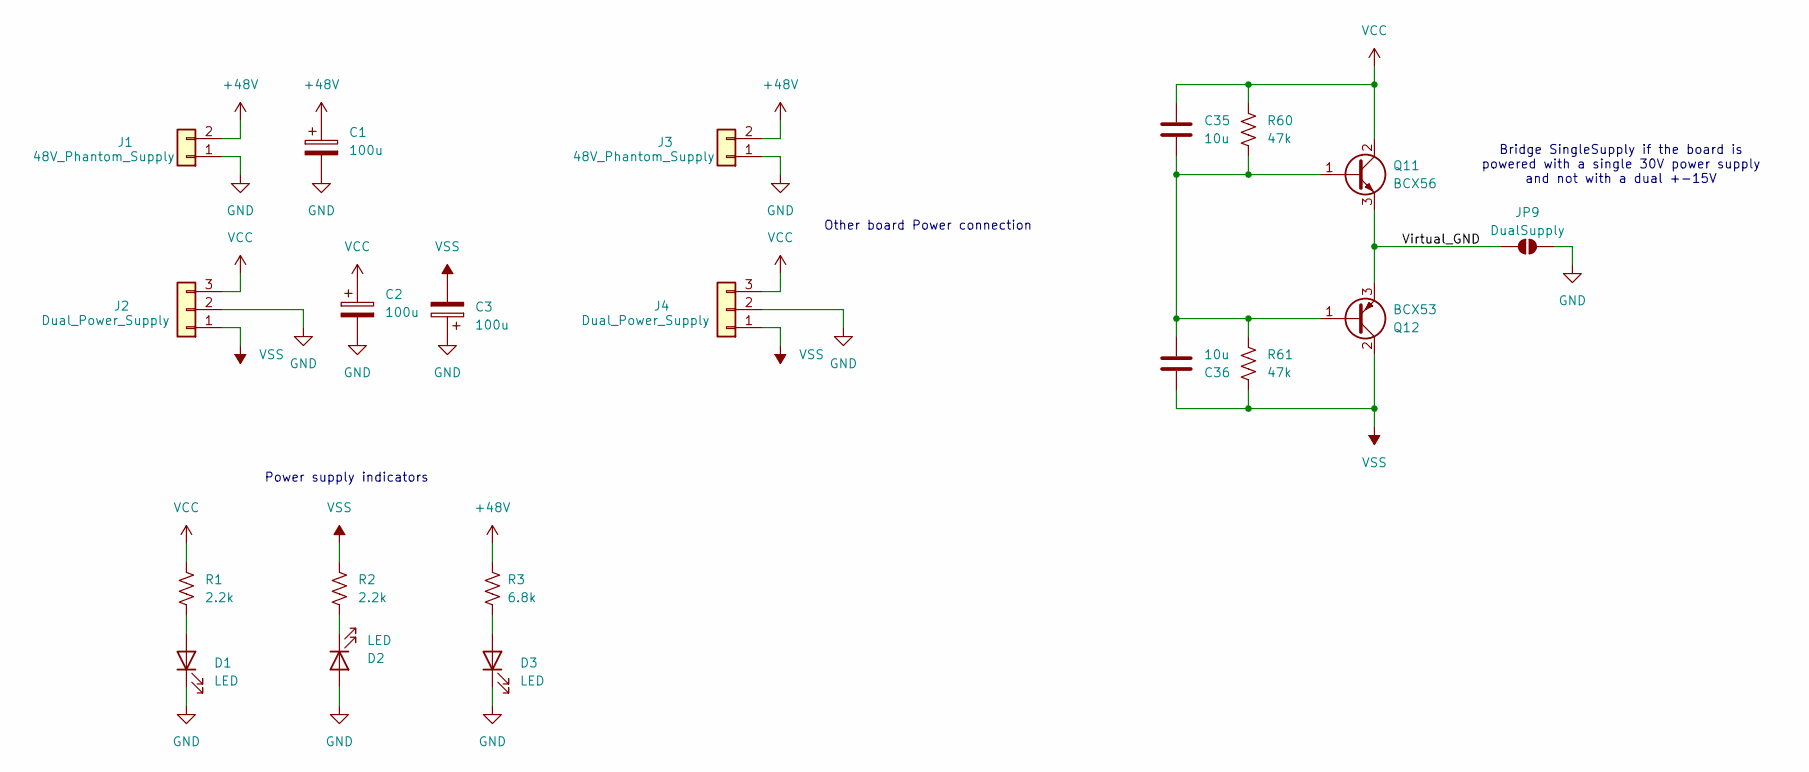
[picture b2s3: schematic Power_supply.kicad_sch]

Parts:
C1, C2, C3: 100u; CP_Radial_D8.0mm_P3.50mm
C35, C36: 10u; C_0805_2012Metric_Pad1.18x1.45mm_HandSolder
D1, D2, D3: LED; LED_D3.0mm
J1, J3: 48V_Phantom_Supply; PinHeader_1x02_P2.54mm_Vertical
J2, J4: Dual_Power_Supply; PinHeader_1x03_P2.54mm_Vertical
JP9: DualSupply; SolderJumper-2_P1.3mm_Open_RoundedPad1.0x1.5mm
Q11: BCX56; SOT-89-3
Q12: BCX53; SOT-89-3
R1, R2: 2.2k; R_1206_3216Metric_Pad1.30x1.75mm_HandSolder
R3: 6.8k; R_1206_3216Metric_Pad1.30x1.75mm_HandSolder
R60, R61: 47k; R_0603_1608Metric_Pad0.98x0.95mm_HandSolder

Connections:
+48V: C1.1, J1.2, J3.2, R3.2; also elsewhere on the board
/Power supply/Virtual_GND: JP9.1 (A), Q11.3 (E), Q12.3 (E)
GND: C1.2, C2.2, C3.1, D1.1 (K), D2.2 (A), D3.1 (K), J1.1, J2.2, J3.1, J4.2, JP9.2 (B); also elsewhere on the board
unnamed: D1.2 (A), R1.1
unnamed: D2.1 (K), R2.1
unnamed: D3.2 (A), R3.1
unnamed: C35.2, C36.2, Q11.1 (B), Q12.1 (B), R60.2, R61.1
VCC: C2.1, C35.1, J2.3, J4.3, Q11.2 (C), R1.2, R60.1; also elsewhere on the board
VSS: C3.2, C36.1, J2.1, J4.1, Q12.2 (C), R2.2, R61.2; also elsewhere on the board

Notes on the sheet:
Bridge SingleSupply if the board is powered with a single 30V power supply and not with a dual +-15V
Other board Power connection
Power supply indicators
